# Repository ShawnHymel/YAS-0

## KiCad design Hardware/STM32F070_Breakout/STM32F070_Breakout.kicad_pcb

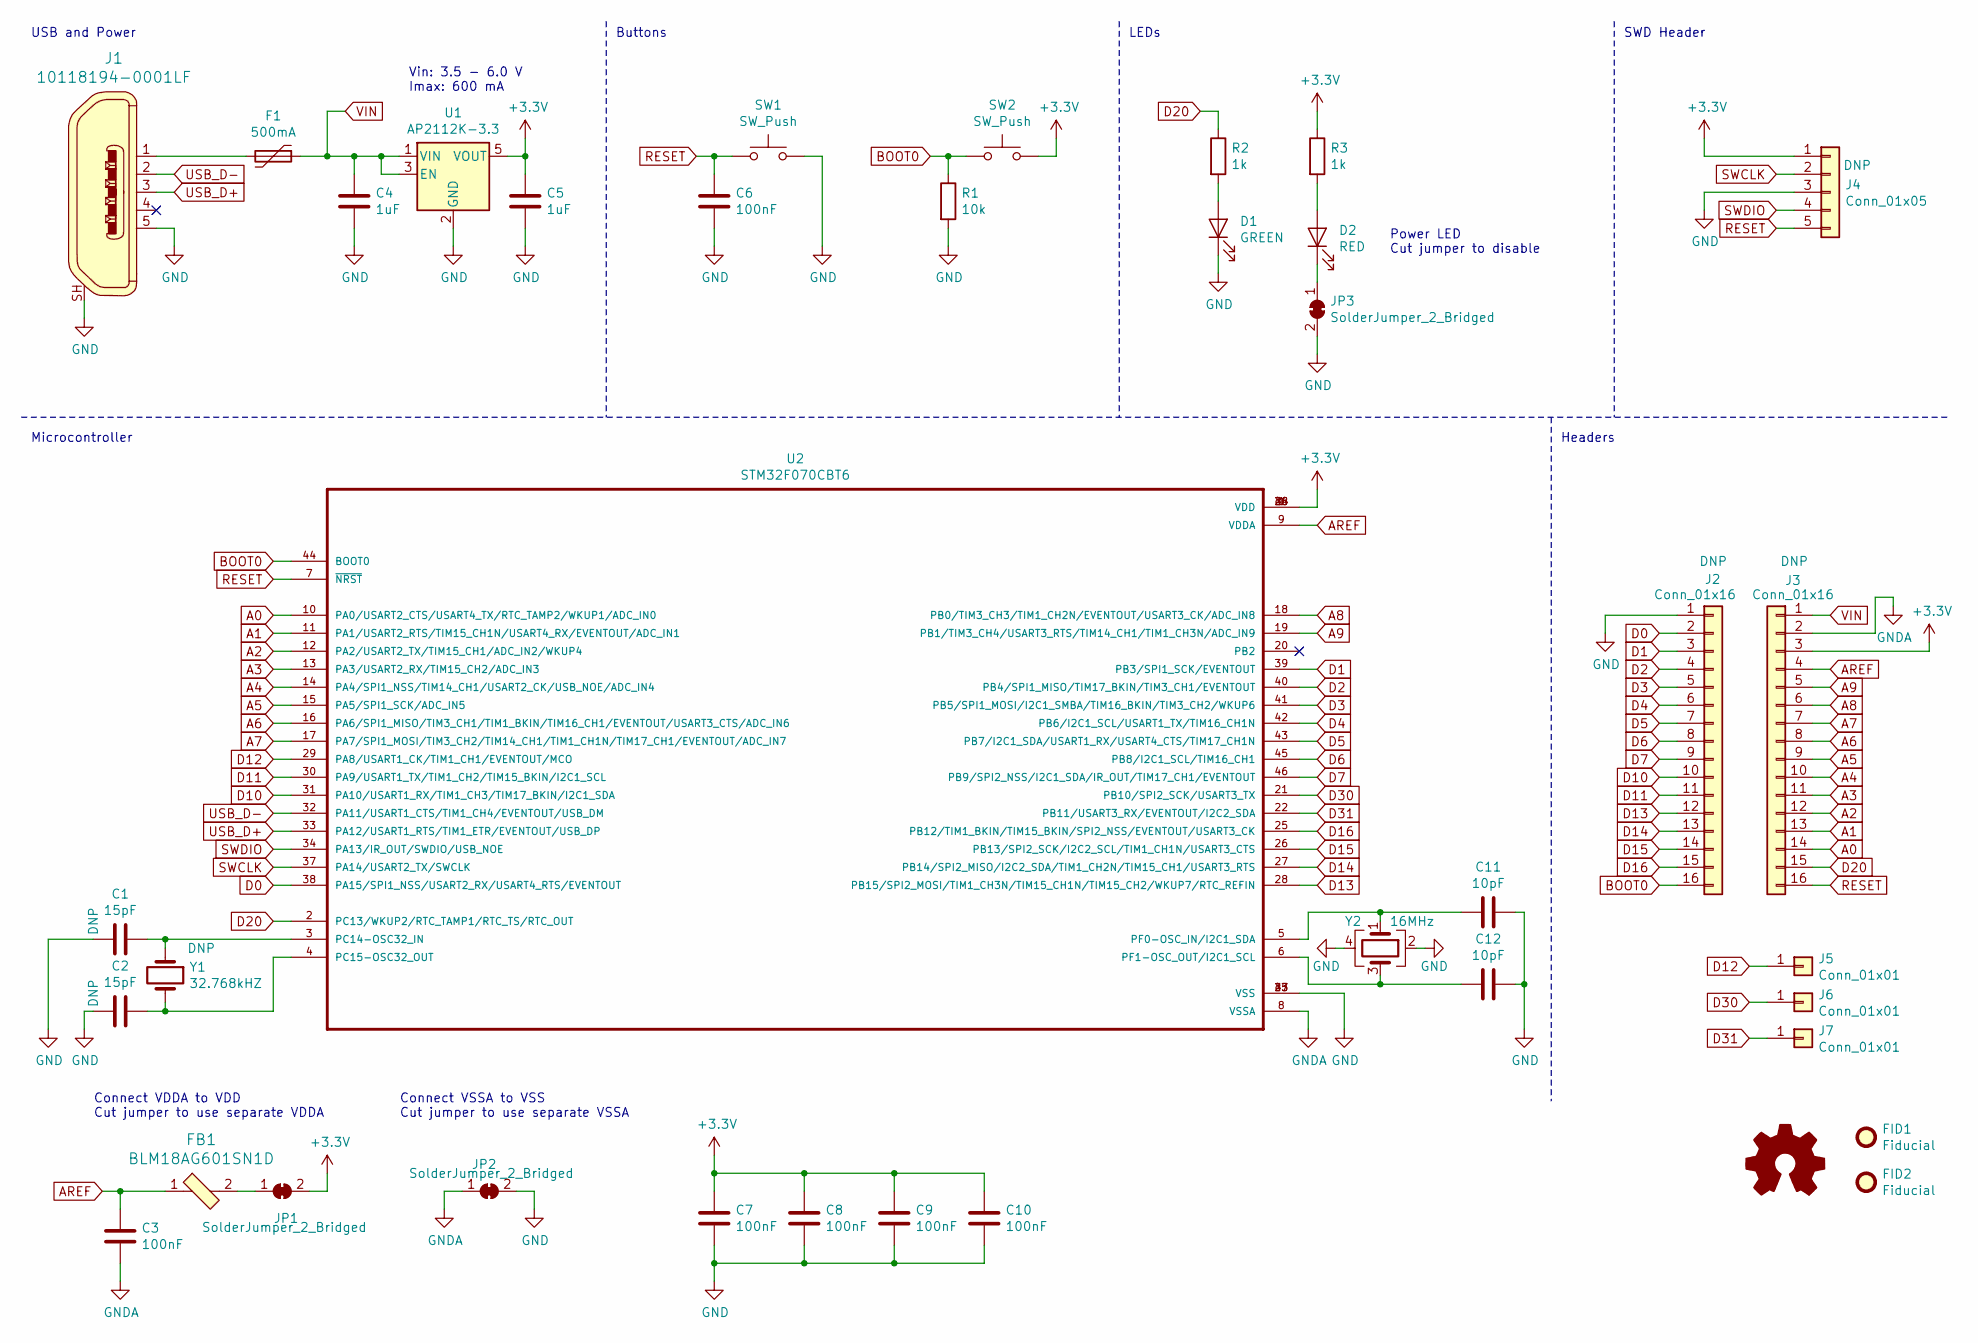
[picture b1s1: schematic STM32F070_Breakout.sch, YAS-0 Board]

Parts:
C1, C2: 15pF; C_0603_1608Metric
C3, C6, C7, C8, C9, C10: 100nF; C_0603_1608Metric
C4, C5: 1uF; C_0603_1608Metric
C11, C12: 10pF; C_0603_1608Metric
D1: GREEN; LED_0603
D2: RED; LED_0603
F1: 500mA; 0ZCK0050FF2E
FB1: BLM18AG601SN1D; R_0603_1608Metric; MPN BLM18AG601SN1D; Digi-Key_PN 490-1014-1-ND
FID1, FID2: Fiducial; Fiducial_1mm_Mask2mm
J1: 10118194-0001LF; USB_Micro_B_Female_10118194-0001LF_oversized_pads; MPN 10118194-0001LF; Digi-Key_PN 609-4618-1-ND
J2, J3: Conn_01x16; PinHeader_1x16_P2.54mm_Vertical_NoSilk
J4: Conn_01x05; PinHeader_1x05_P2.54mm_Vertical_NoSilk
J5, J6, J7: Conn_01x01; TestPoint_Pad_1.0x2.5mm
JP1, JP2, JP3: SolderJumper_2_Bridged; SolderJumper-2_P1.3mm_Bridged_RoundedPad1.0x1.5mm
R1: 10k; R_0603_1608Metric
R2, R3: 1k; R_0603_1608Metric
SW1, SW2: SW_Push; SW_SPST_PTS810
U1: AP2112K-3.3; SOT-23-5
U2: STM32F070CBT6; QFP50P900X900X160-48N
Y1: 32.768kHZ; Crystal_SMD_G8-2Pin_3.2x1.5mm
Y2: 16MHz; Crystal_SMD_SeikoEpson_TSX3225-4Pin_3.2x2.5mm

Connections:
+3V3: C5.1, C7.1, C8.1, C9.1, C10.1, J3.3, J4.1, JP1.2 (B), R3.1, SW2.2, U1.5 (VOUT), U2.1 (VDD), U2.24 (VDD), U2.36 (VDD), U2.48 (VDD)
A0: J3.14, U2.10 (PA0/USART2_CTS/USART4_TX/RTC_TAMP2/WKUP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)
A1: J3.13, U2.11 (PA1/USART2_RTS/TIM15_CH1N/USART4_RX/EVE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)
A2: J3.12, U2.12 (PA2/USART2_TX/TIM15_CH1/ADC_IN2/WKUP4)
A3: J3.11, U2.13 (PA3/USART2_RX/TIM15_CH2/ADC_IN3)
A4: J3.10, U2.14 (PA4/SPI1_NSS/TIM14_CH1/USART2_CK/USB_NO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)
A5: J3.9, U2.15 (PA5/SPI1_SCK/ADC_IN5)
A6: J3.8, U2.16 (PA6/SPI1_MISO/TIM3_CH1/TIM1_BKIN/TIM16_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)
A7: J3.7, U2.17 (PA7/SPI1_MOSI/TIM3_CH2/TIM14_CH1/TIM1_C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)
A8: J3.6, U2.18 (PB0/TIM3_CH3/TIM1_CH2N/EVENTOUT/USART3_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)
A9: J3.5, U2.19 (PB1/TIM3_CH4/USART3_RTS/TIM14_CH1/TIM1_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)
AREF: C3.1, FB1.1, J3.4, U2.9 (VDDA)
BOOT0: J2.16, R1.1, SW2.1, U2.44 (BOOT0)
D0: J2.2, U2.38 (PA15/SPI1_NSS/USART2_RX/USART4_RTS/EVEN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)
D1: J2.3, U2.39 (PB3/SPI1_SCK/EVENTOUT)
D2: J2.4, U2.40 (PB4/SPI1_MISO/TIM17_BKIN/TIM3_CH1/EVENT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)
D3: J2.5, U2.41 (PB5/SPI1_MOSI/I2C1_SMBA/TIM16_BKIN/TIM3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)
D4: J2.6, U2.42 (PB6/I2C1_SCL/USART1_TX/TIM16_CH1N)
D5: J2.7, U2.43 (PB7/I2C1_SDA/USART1_RX/USART4_CTS/TIM17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)
D6: J2.8, U2.45 (PB8/I2C1_SCL/TIM16_CH1)
D7: J2.9, U2.46 (PB9/SPI2_NSS/I2C1_SDA/IR_OUT/TIM17_CH1/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)
D10: J2.10, U2.31 (PA10/USART1_RX/TIM1_CH3/TIM17_BKIN/I2C1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)
D11: J2.11, U2.30 (PA9/USART1_TX/TIM1_CH2/TIM15_BKIN/I2C1_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)
D12: J5.1, U2.29 (PA8/USART1_CK/TIM1_CH1/EVENTOUT/MCO)
D13: J2.12, U2.28 (PB15/SPI2_MOSI/TIM1_CH3N/TIM15_CH1N/TIM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)
D14: J2.13, U2.27 (PB14/SPI2_MISO/I2C2_SDA/TIM1_CH2N/TIM15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)
D15: J2.14, U2.26 (PB13/SPI2_SCK/I2C2_SCL/TIM1_CH1N/USART3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)
D16: J2.15, U2.25 (PB12/TIM1_BKIN/TIM15_BKIN/SPI2_NSS/EVEN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)
D20: J3.15, R2.1, U2.2 (PC13/WKUP2/RTC_TAMP1/RTC_TS/RTC_OUT)
D30: J6.1, U2.21 (PB10/SPI2_SCK/USART3_TX)
D31: J7.1, U2.22 (PB11/USART3_RX/EVENTOUT/I2C2_SDA)
GND: C1.2, C2.2, C4.2, C5.2, C6.2, C7.2, C8.2, C9.2, C10.2, C11.1, C12.1, D1.1 (K), J1.5, J1.SH, J2.1, J4.3, JP2.2 (B), JP3.2 (B), R1.2, SW1.2, U1.2 (GND), U2.23 (VSS), U2.35 (VSS), U2.47 (VSS), Y2.2, Y2.4
GNDA: C3.2, J3.2, JP2.1 (A), U2.8 (VSSA)
unnamed: C1.1, U2.3 (PC14-OSC32_IN), Y1.1
unnamed: C2.1, U2.4 (PC15-OSC32_OUT), Y1.2
unnamed: C11.2, U2.5 (PF0-OSC_IN/I2C1_SDA), Y2.1
unnamed: C12.2, U2.6 (PF1-OSC_OUT/I2C1_SCL), Y2.3
unnamed: D1.2 (A), R2.2
unnamed: D2.1 (K), JP3.1 (A)
unnamed: D2.2 (A), R3.2
unnamed: F1.2, J1.1
unnamed: FB1.2, JP1.1 (A)
RESET: C6.1, J3.16, J4.5, SW1.1, U2.7 (~NRST~)
SWCLK: J4.2, U2.37 (PA14/USART2_TX/SWCLK)
SWDIO: J4.4, U2.34 (PA13/IR_OUT/SWDIO/USB_NOE)
USB_D+: J1.3, U2.33 (PA12/USART1_RTS/TIM1_ETR/EVENTOUT/USB_DP)
USB_D-: J1.2, U2.32 (PA11/USART1_CTS/TIM1_CH4/EVENTOUT/USB_DM)
VIN: C4.1, F1.1, J3.1, U1.1 (VIN), U1.3 (EN)

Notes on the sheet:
Power LED Cut jumper to disable
SWD Header
LEDs
USB and Power
Headers
Buttons
Connect VDDA to VDD Cut jumper to use separate VDDA
Connect VSSA to VSS Cut jumper to use separate VSSA
Microcontroller
Vin: 3.5 - 6.0 V Imax: 600 mA

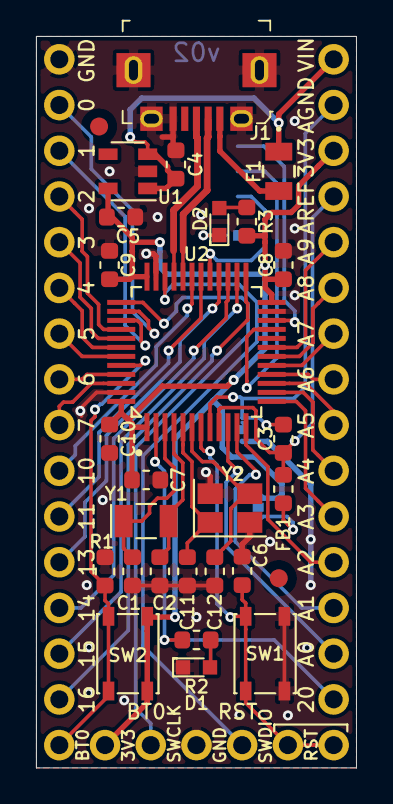
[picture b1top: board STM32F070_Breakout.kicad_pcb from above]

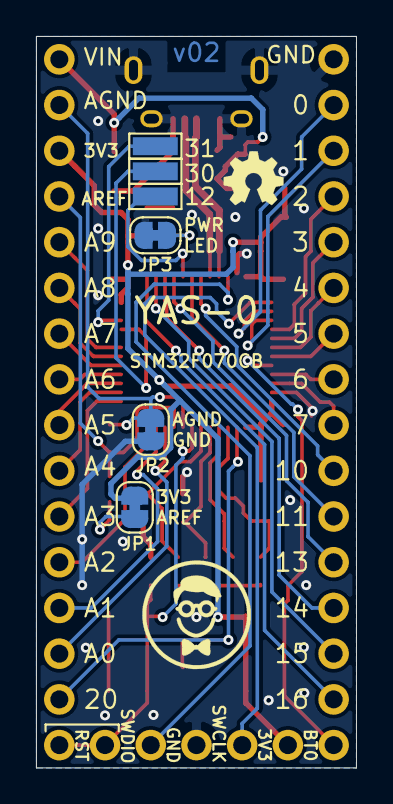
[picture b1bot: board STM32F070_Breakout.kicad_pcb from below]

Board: 2 copper layers, 17.8 x 40.6 mm, 37 parts (6 on the bottom side), 48 nets.

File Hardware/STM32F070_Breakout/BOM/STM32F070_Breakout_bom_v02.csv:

Component,Description,Part,References,Value,Footprint,Quantity Per PCB,Datasheet,Config,Category,Status,Family,MPN,Digi-Key_PN,DK_Datasheet_Link,DK_Detail_Page,Manufacturer,$/1 (@1),$/1 (@1k),Total (@1k)
1,Unpolarized capacitor,C,C3 C6 C7 C8 C9 C10,100nF,C_0603_1608Metric,6,~,,,,,CL10B104KO8NNNC,1276-1005-1-ND,,,,$0.1000,$0.0073,$0.04
2,Unpolarized capacitor,C,C11 C12,10pF,C_0603_1608Metric,2,~,,,,,CL10C100JB8NNNC,1276-1027-1-ND,,,,$0.1000,$0.0101,$0.02
3,Unpolarized capacitor,C,C4 C5,1uF,C_0603_1608Metric,2,~,,,,,CL10A105KP8NNNC,1276-1182-1-ND,,,,$0.1000,$0.0094,$0.02
4,Light emitting diode,LED,D1,GREEN,LED_0603,1,~,,,,,LTST-C190KGKT,160-1435-1-ND,,,,$0.2700,$0.0486,$0.05
5,Light emitting diode,LED,D2,RED,LED_0603,1,~,,,,,LTST-C190KRKT,160-1436-1-ND,,,,$0.2700,$0.0486,$0.05
6,"Resettable fuse, polymeric positive temperature coefficient",Polyfuse,F1,500mA,0ZCK0050FF2E,1,~,,,,,0ZCK0050FF2E,507-1813-1-ND,,,,$0.2100,$0.1163,$0.12
7,FERRITE BEAD 600 OHM 0603 1LN,BLM18AG601SN1D,FB1,BLM18AG601SN1D,R_0603_1608Metric,1,https://www.murata.com/en-us/products/productdata/8796738650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,,Filters,Active,Ferrite Beads and Chips,BLM18AG601SN1D,490-1014-1-ND,https://www.murata.com/en-us/products/productdata/8796738650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,/product-detail/en/murata-electronics-north-america/BLM18AG601SN1D/490-1014-1-ND/584462,Murata Electronics North America,$0.1000,$0.0274,$0.03
8,CONN RCPT USB2.0 MICRO B SMD R/A,10118194-0001LF,J1,10118194-0001LF,USB_Micro_B_Female_10118194-0001LF_oversized_pads,1,http://www.amphenol-icc.com/media/wysiwyg/files/drawing/1011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,,"Connectors, Interconnects",Active,"USB, DVI, HDMI Connectors",10118194-0001LF,609-4618-1-ND,http://www.amphenol-icc.com/media/wysiwyg/files/drawing/1011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,/product-detail/en/amphenol-icc-fci/10118194-0001LF/609-4618-1-ND/2785382,Amphenol ICC (FCI),$0.4200,$0.2084,$0.21
9,Resistor,R,R1,10k,R_0603_1608Metric,1,~,,,,,RC0603FR-0710KL,311-10.0KHRCT-ND,,,,$0.1000,$0.0044,$0.00
10,Resistor,R,R2 R3,1k,R_0603_1608Metric,2,~,,,,,RC0603FR-071KL,311-1.00KHRCT-ND,,,,$0.1000,$0.0038,$0.01
11,"Push button switch, generic, two pins",SW_Push,SW1 SW2,SW_Push,SW_SPST_PTS810,2,~,,,,,PTS810 SJM 250 SMTR LFS,CKN10502CT-ND,,,,$0.3000,$0.1730,$0.35
12,"600mA low dropout linear regulator, with enable pin, 3.8V-6V input voltage range, 3.3V fixed positive output, SOT-23-5 package",AP2112K-3.3,U1,AP2112K-3.3,SOT-23-5,1,https://www.diodes.com/assets/Datasheets/AP2112.pdf,,,,,AP2112K-3.3TRG1,AP2112K-3.3TRG1DICT-ND,,,,$0.4800,$0.1187,$0.12
13,,STM32F070CBT6,U2,STM32F070CBT6,QFP50P900X900X160-48N,1,Unavailable,,,,,STM32F070CBT6,497-15099-ND,,,,$2.5200,$1.2411,$1.24
14,"Four pin crystal, GND on pins 2 and 4",Crystal_GND24,Y2,16MHz,Crystal_SMD_SeikoEpson_TSX3225-4Pin_3.2x2.5mm,1,~,,,,,TSX-3225 16.0000MF09Z-AC0,SER4069CT-ND,,,,$0.3600,$0.1760,$0.18
,,,,,,,,,,,,,,,,,,,
,,,,,,,,,,,,,,,,,,Total:,$2.43
,,,,,,,,,,,,,,,,,,,
,,,,,,,,,,,,,,,,,,,
,,,,,,,,,,,,,,,,,,,
Component Groups:,18,,,,,,,,,,,,,,,,,,
Component Count:,29,,,,,,,,,,,,,,,,,,
Fitted Components:,23,,,,,,,,,,,,,,,,,,
Number of PCBs:,1,,,,,,,,,,,,,,,,,,
Total components:,23,,,,,,,,,,,,,,,,,,
Schematic Version:,v02,,,,,,,,,,,,,,,,,,
Schematic Date:,5/30/2019,,,,,,,,,,,,,,,,,,
PCB Variant:,['default'],,,,,,,,,,,,,,,,,,
BoM Date:,8/8/2019 13:49,,,,,,,,,,,,,,,,,,
Schematic Source:,C:\Users\sgmustadio\Documents\GitHub\YAS-0\Hardware\STM32F070_Breakout\STM32F070_Breakout.sch,,,,,,,,,,,,,,,,,,
KiCad Version:,Eeschema (5.1.0)-1,,,,,,,,,,,,,,,,,,

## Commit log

2019-06-01 Initial commit. Almost done with schematic.
2019-06-01 Finished schematic
2019-06-01 Associated symbols with footprints
2019-06-04 Moved components around. Created BOM.
2019-06-05 Components placed
2019-06-06 Layout done
2019-06-07 Version v01 complete and sent for fab.
2019-08-07 Finished v02 layout
2019-08-29 Added schematic pdf

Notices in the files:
Hardware/STM32F070_Breakout/STM32F070_Breakout.kicad_pcb:
License: CC BY 4.0
Hardware/STM32F070_Breakout/STM32F070_Breakout.sch:
creativecommons.org/licenses/by/4.0
parts and their libraries:
Copyright 2016 Accelerated Designs. All rights reserved.
